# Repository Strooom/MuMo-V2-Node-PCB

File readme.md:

# Lora-based environmental monitor
* intended for monitoring collection items in musea. Other applications are possible but the unit is currently designed for indoor use only
* monitors temperature, relative humidity, VOC gasses, barometric pressure, light intensity and others
	- BME680 and TSL25911 sensors are built in, other can be added through I2C or UART
* runs on a single cell LiFePO4 battery. Battery-charger from USB-C port included
* Wio-E5 LoRa module from www.seeedstudio.com. This contains an STM32WLE processor combined with Semtech SX126X radio. The firmware runs directly on the STM32. More info on this Wio-E5 :  https://www.seeedstudio.com/LoRa-E5-Wireless-Module-p-4745.html
* 128 KByte of onboard EEPROM allows to buffer sensor-readings when network is unavailable.
* ePaper display allows to identify the device, and read status from the display, while still being ultra low power.

The related firmware for this device can be found in https://github.com/Strooom/MuMo-v2-Node-SW

More info can be found in the Wiki : 
https://github.com/Strooom/MuMo-V2-Node-PCB/wiki

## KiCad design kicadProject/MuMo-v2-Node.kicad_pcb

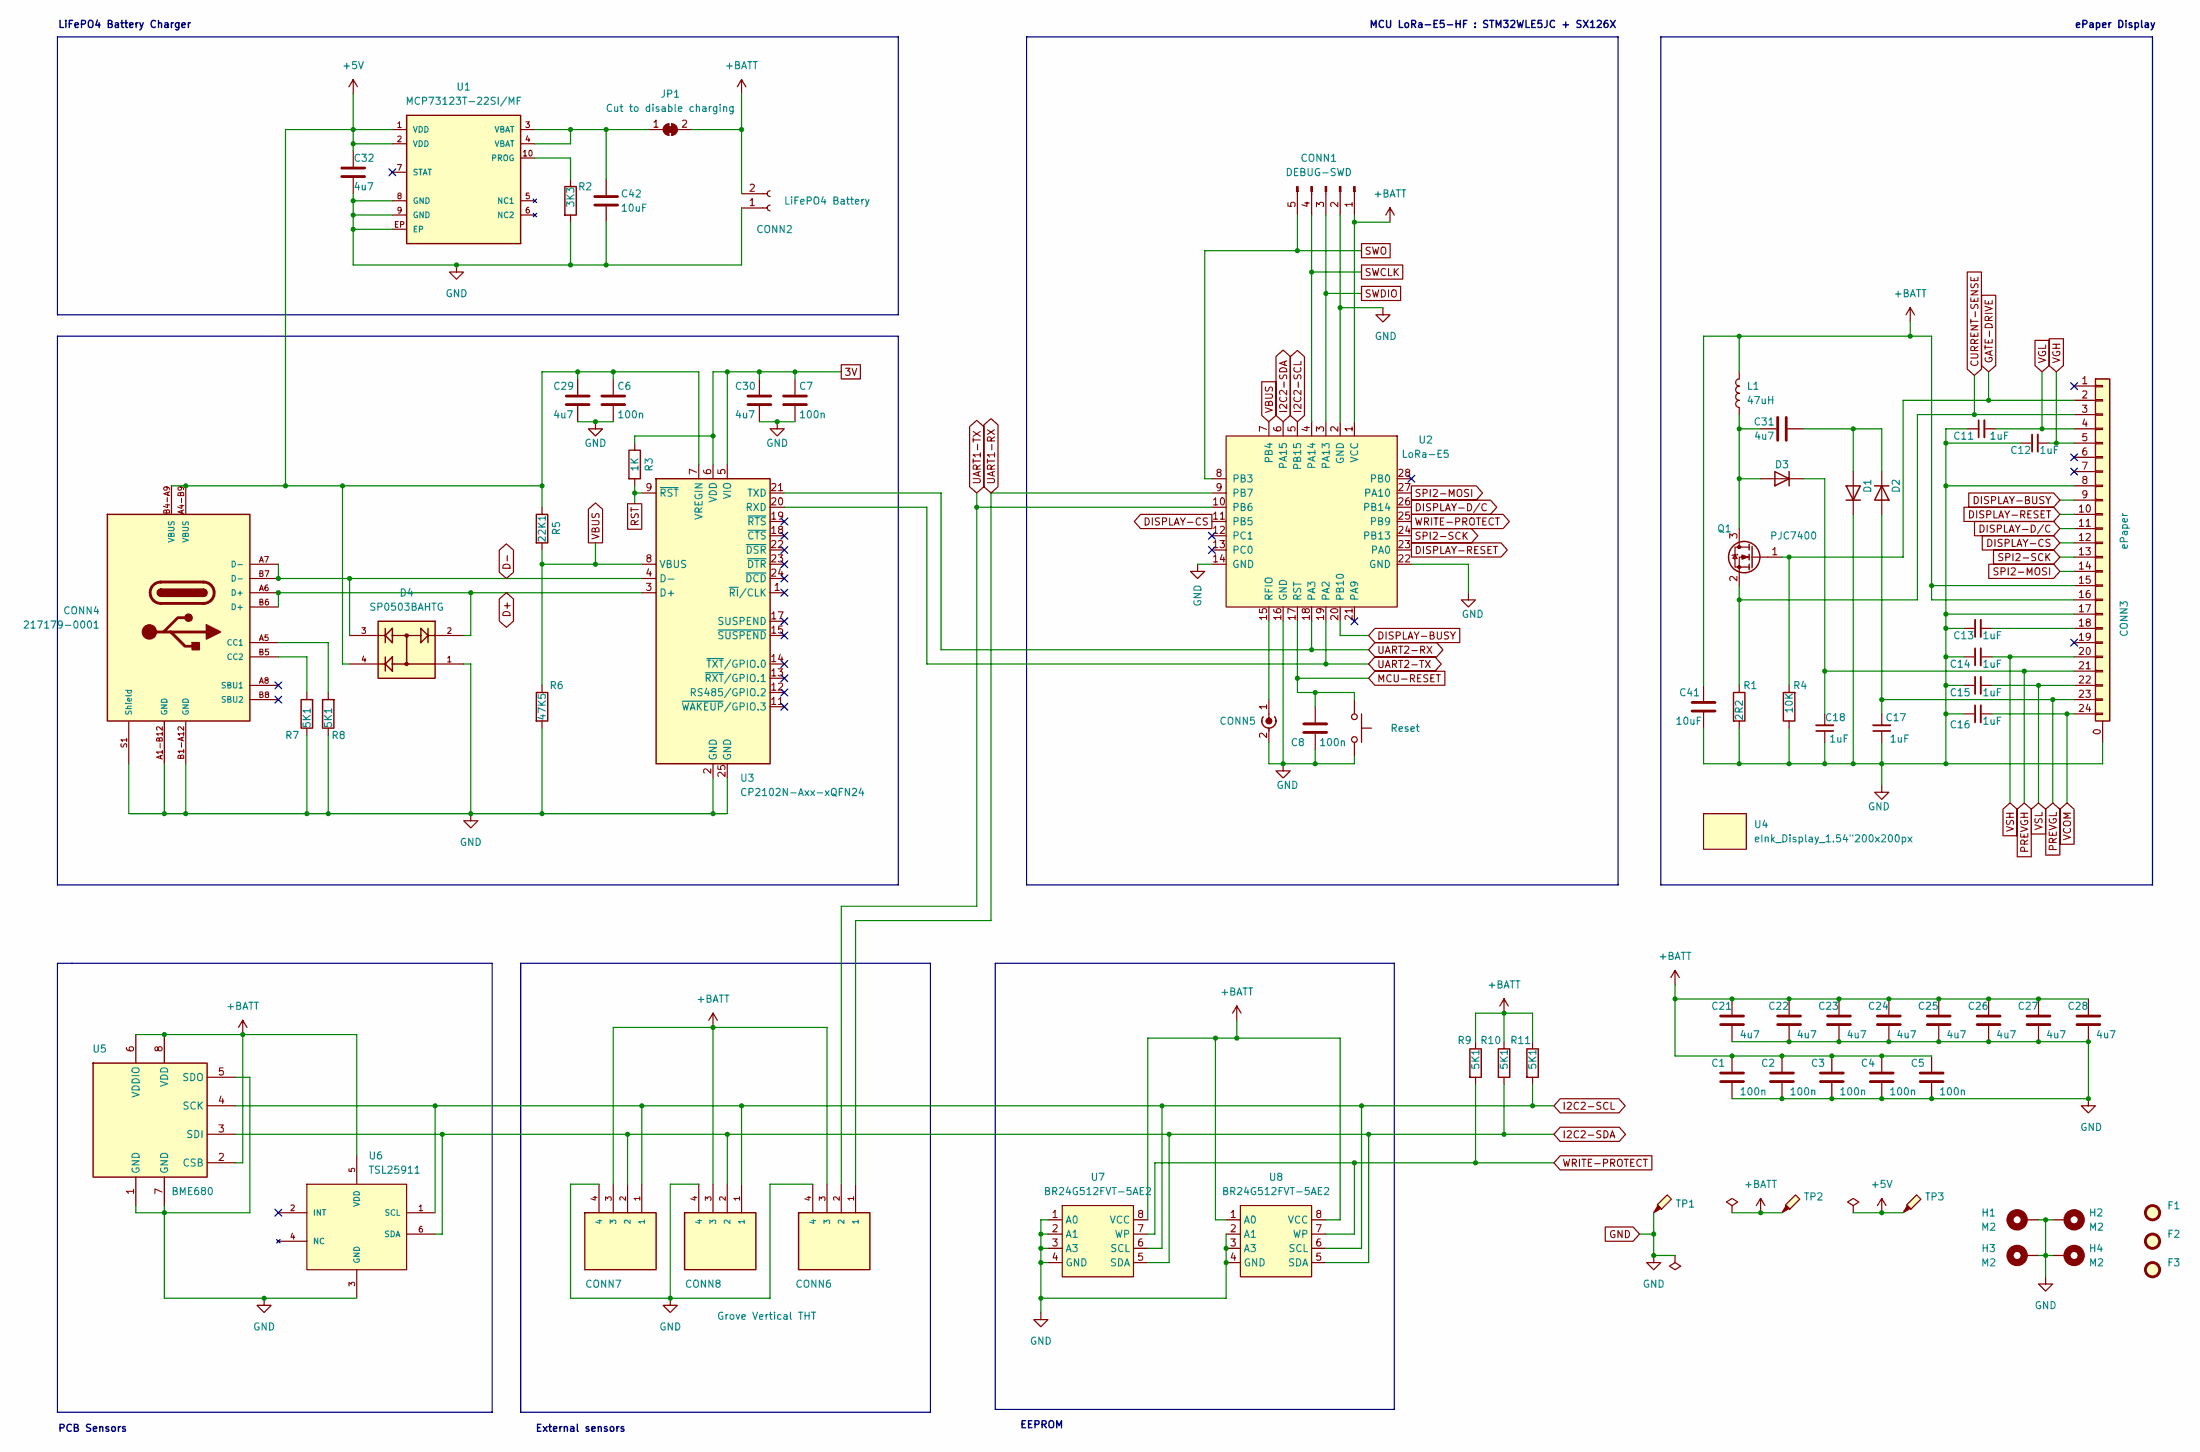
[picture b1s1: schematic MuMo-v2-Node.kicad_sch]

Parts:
C1, C2, C3, C4, C5, C6, C7, C8: 100n; 0603_1608Metric; MPN CGA3E2X7R1E104K080AA
C11, C12, C13, C14, C15, C16, C17, C18: 1uF; 0603_1608Metric; MPN CGA3E1X7R1E105K080AC
C21, C22, C23, C24, C25, C26, C27, C28, C29, C30, C31, C32: 4u7; 0603_1608Metric; MPN C1608X7S1A475K080AC
C41, C42: 10uF; 0603_1608Metric; MPN C1608X6S1A106M080AC
CONN1: DEBUG-SWD; PinHeader_1x05_P2.54mm_Vertical; MPN 10129378-905002BLF
CONN2: B2B-XH-A (LF)(SN); JST_XH_B2B-XH-A_1x02_P2.50mm_Vertical; MPN B2B-XH-A (LF)(SN)
CONN3: ePaper; TE_2-1734839-4_1x24-1MP_P0.5mm_Horizontal; MPN 2-1734839-4
CONN4: 217179-0001; Molex-2171790001; PARTREV A3
CONN5: Conn_Coaxial_Power; LINX_CONSMA020.062-G; MPN CONSMA020.062-G
CONN6, CONN7, CONN8: Grove Vertical THT; SEEED_110990030; MPN 110990030
D1, D2, D3: SS1FL3HM3/H; D_SMF; MPN SL03-GS08
D4: SP0503BAHTG; SP0503BAHTG-SOT143; PARTREV N/A
F1, F2, F3: Fiducial; Fiducial_0.75mm_Mask1.5mm; MPN notApplicable
H1, H2, H3, H4: M2; MountingHole_2.2mm_M2_Pad; MPN notApplicable
JP1: Cut to disable charging; SolderJumper-2_P1.3mm_Bridged2Bar_Pad1.0x1.5mm; MPN notApplicable
L1: 47uH; L_TDK_VLS6045EX; MPN VLS6045EX-470M
Q1: PJC7400; SOT-323_SC-70; MPN PJC7400_R1_00001
R1: 2R2; 0603_1608Metric; MPN ERJ-3RQJ2R2V
R2: 3K3; 0603_1608Metric; MPN CR0603-JW-332ELF
R3: 1K; 0603_1608Metric; MPN CR0603-JW-102ELF
R4: 10K; 0603_1608Metric; MPN CR0603-JW-103ELF
R5: 22K1; 0603_1608Metric; MPN CR0603-FX-2212ELF
R6: 47K5; 0603_1608Metric; MPN CR0603-FX-4752ELF
R7, R8, R9, R10, R11: 5K1; 0603_1608Metric; MPN CR0603-FX-5101ELF
SW1: Reset; SW_SPST_PTS815; MPN PTS815 SJM 250 SMTR LFS
TP1, TP2, TP3: testPad; TestPoint_THTPad_1.5x1.5mm_Drill0.7mm; MPN notApplicable
U1: MCP73123T-22SI/MF; DFN10 - MCP73123; MPN MCP73123T-22SI/MF
U2: LoRa-E5; MPN 317990687
U3: CP2102N-Axx-xQFN24; QFN24 - CP2102N; MPN CP2102N-A02-GQFN24R
U4: eInk_Display_1.54"200x200px; OSHW-Symbol_6.7x6mm_SilkScreen; MPN GDEH0154D67
U5: BME680; Bosch_BME680; MPN BME680
U6: TSL25911; TSL2591-SON; MPN TSL25911FN
U7, U8: BR24G512FVT-5AE2; TSSOP-B8; MPN BR24G512FVT-5AE2

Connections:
3V: C7.1, C30.1, R3.1, U3.5 (VIO), U3.6 (VDD)
+5V: C6.1, C29.1, C32.1, CONN4.A4-B9 (VBUS), CONN4.B4-A9 (VBUS), D4.4, R5.1, TP3.1, U1.1 (VDD), U1.2 (VDD), U3.7 (VREGIN)
+BATT: C1.1, C2.1, C3.1, C4.1, C5.1, C21.1, C22.1, C23.1, C24.1, C25.1, C26.1, C27.1, C28.1, C41.1, CONN1.1, CONN2.2 (+), CONN3.15, CONN3.16, CONN6.3, CONN7.3, CONN8.3, JP1.2 (B), L1.2, R9.1, R10.1, R11.1, TP2.1, U2.1 (VCC), U5.2 (CSB), U5.6 (VDDIO), U5.8 (VDD), U6.5 (VDD), U7.8 (VCC), U8.1 (A0), U8.8 (VCC)
CURRENT-SENSE: CONN3.3, Q1.2 (S), R1.1
D+: CONN4.A6 (D+), CONN4.B6 (D+), D4.2, U3.3 (D+)
D-: CONN4.A7 (D-), CONN4.B7 (D-), D4.3, U3.4 (D-)
DISPLAY-BUSY: CONN3.9, U2.20 (PB10)
DISPLAY-CS: CONN3.12, U2.11 (PB5)
DISPLAY-D/C: CONN3.11, U2.26 (PB14)
DISPLAY-RESET: CONN3.10, U2.23 (PA0)
GATE-DRIVE: CONN3.2, Q1.1 (G), R4.2
GND: C1.2, C2.2, C3.2, C4.2, C5.2, C6.2, C7.2, C8.2, C11.1, C12.1, C13.1, C14.1, C15.1, C16.1, C17.1, C18.1, C21.2, C22.2, C23.2, C24.2, C25.2, C26.2, C27.2, C28.2, C29.2, C30.2, C32.2, C41.2, C42.2, CONN1.2, CONN2.1 (-), CONN3.0 (GND), CONN3.8, CONN3.17, CONN4.A1-B12 (GND), CONN4.B1-A12 (GND), CONN4.S1 (Shield), CONN5.2 (Ext), CONN6.4, CONN7.4, CONN8.4, D1.1 (K), D4.1, H1.1, H2.1, H3.1, H4.1, R1.2, R2.2, R4.1, R6.2, R7.1, R8.1, SW1.1, TP1.1, U1.8 (GND), U1.9 (GND), U1.EP, U2.2 (GND), U2.14 (GND), U2.16 (GND), U2.22 (GND), U3.2 (GND), U3.25 (GND), U5.1 (GND), U5.5 (SDO), U5.7 (GND), U6.3 (GND), U7.1 (A0), U7.2 (A1), U7.3 (A3), U7.4 (GND), U8.2 (A1), U8.3 (A3), U8.4 (GND)
I2C2-SCL: CONN7.1, CONN8.1, R11.2, U2.5 (PB15), U5.4 (SCK), U6.1 (SCL), U7.6 (SCL), U8.6 (SCL)
I2C2-SDA: CONN7.2, CONN8.2, R10.2, U2.6 (PA15), U5.3 (SDI), U6.6 (SDA), U7.5 (SDA), U8.5 (SDA)
MCU-RESET: C8.1, SW1.2, U2.17 (RST)
unnamed: C13.2, CONN3.18
unnamed: CONN4.A5 (CC1), R8.2
unnamed: CONN4.B5 (CC2), R7.2
unnamed: CONN5.1 (In), U2.15 (RFIO)
unnamed: C31.1, D1.2 (A), D2.1 (K)
unnamed: C31.2, D3.2 (A), L1.1, Q1.3 (D)
unnamed: C42.1, JP1.1 (A), U1.3 (VBAT), U1.4 (VBAT)
unnamed: R2.1, U1.10 (PROG)
PREVGH: C18.2, CONN3.21, D3.1 (K)
PREVGL: C17.2, CONN3.23, D2.2 (A)
RST: R3.2, U3.9 (~RST)
SPI2-MOSI: CONN3.14, U2.27 (PA10)
SPI2-SCK: CONN3.13, U2.24 (PB13~)
SWCLK: CONN1.4, U2.4 (PA14)
SWDIO: CONN1.3, U2.3 (PA13)
SWO: CONN1.5, U2.8 (PB3)
UART1-RX: CONN6.1, U2.9 (PB7)
UART1-TX: CONN6.2, U2.10 (PB6)
UART2-RX: U2.18 (PA3), U3.21 (TXD)
UART2-TX: U2.19 (PA2), U3.20 (RXD)
VBUS: R5.2, R6.1, U2.7 (PB4), U3.8 (VBUS)
VCOM: C16.2, CONN3.24
VGH: C12.2, CONN3.5
VGL: C11.2, CONN3.4
VSH: C14.2, CONN3.20
VSL: C15.2, CONN3.22
WRITE-PROTECT: R9.2, U2.25 (PB9), U7.7 (WP), U8.7 (WP)

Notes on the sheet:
ePaper Display
LiFePO4 Battery Charger
EEPROM
External sensors
PCB Sensors
MCU LoRa-E5-HF : STM32WLE5JC + SX126X

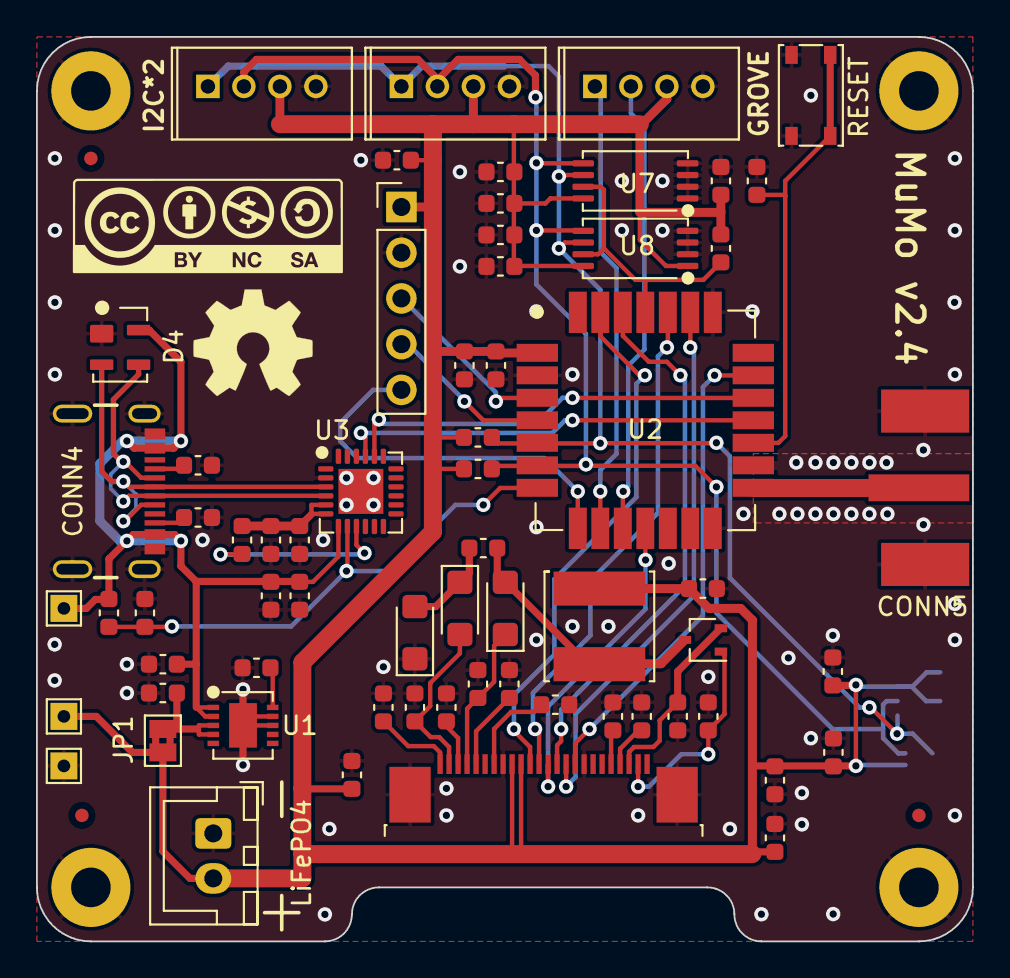
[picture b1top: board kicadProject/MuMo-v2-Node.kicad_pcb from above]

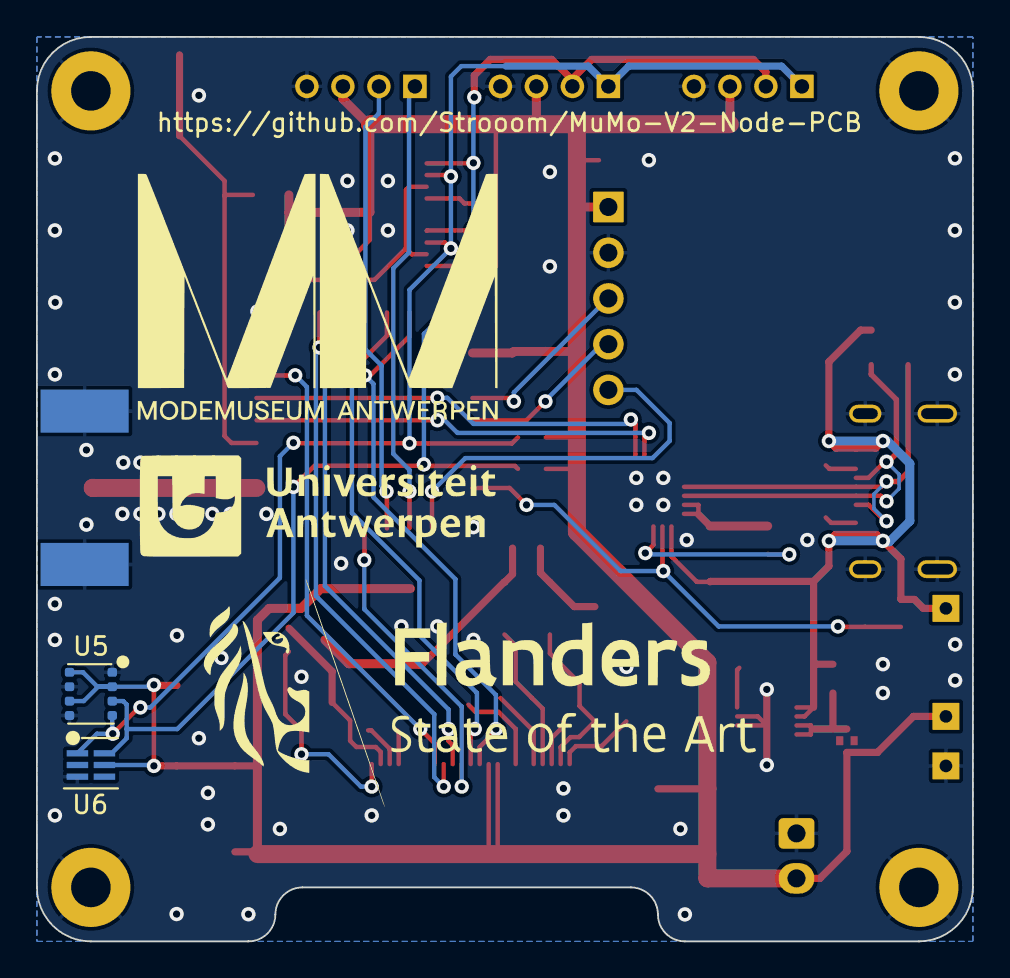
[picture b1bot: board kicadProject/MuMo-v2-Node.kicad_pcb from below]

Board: 2 copper layers, 52.0 x 50.3 mm, 75 parts (2 on the bottom side), 42 nets.

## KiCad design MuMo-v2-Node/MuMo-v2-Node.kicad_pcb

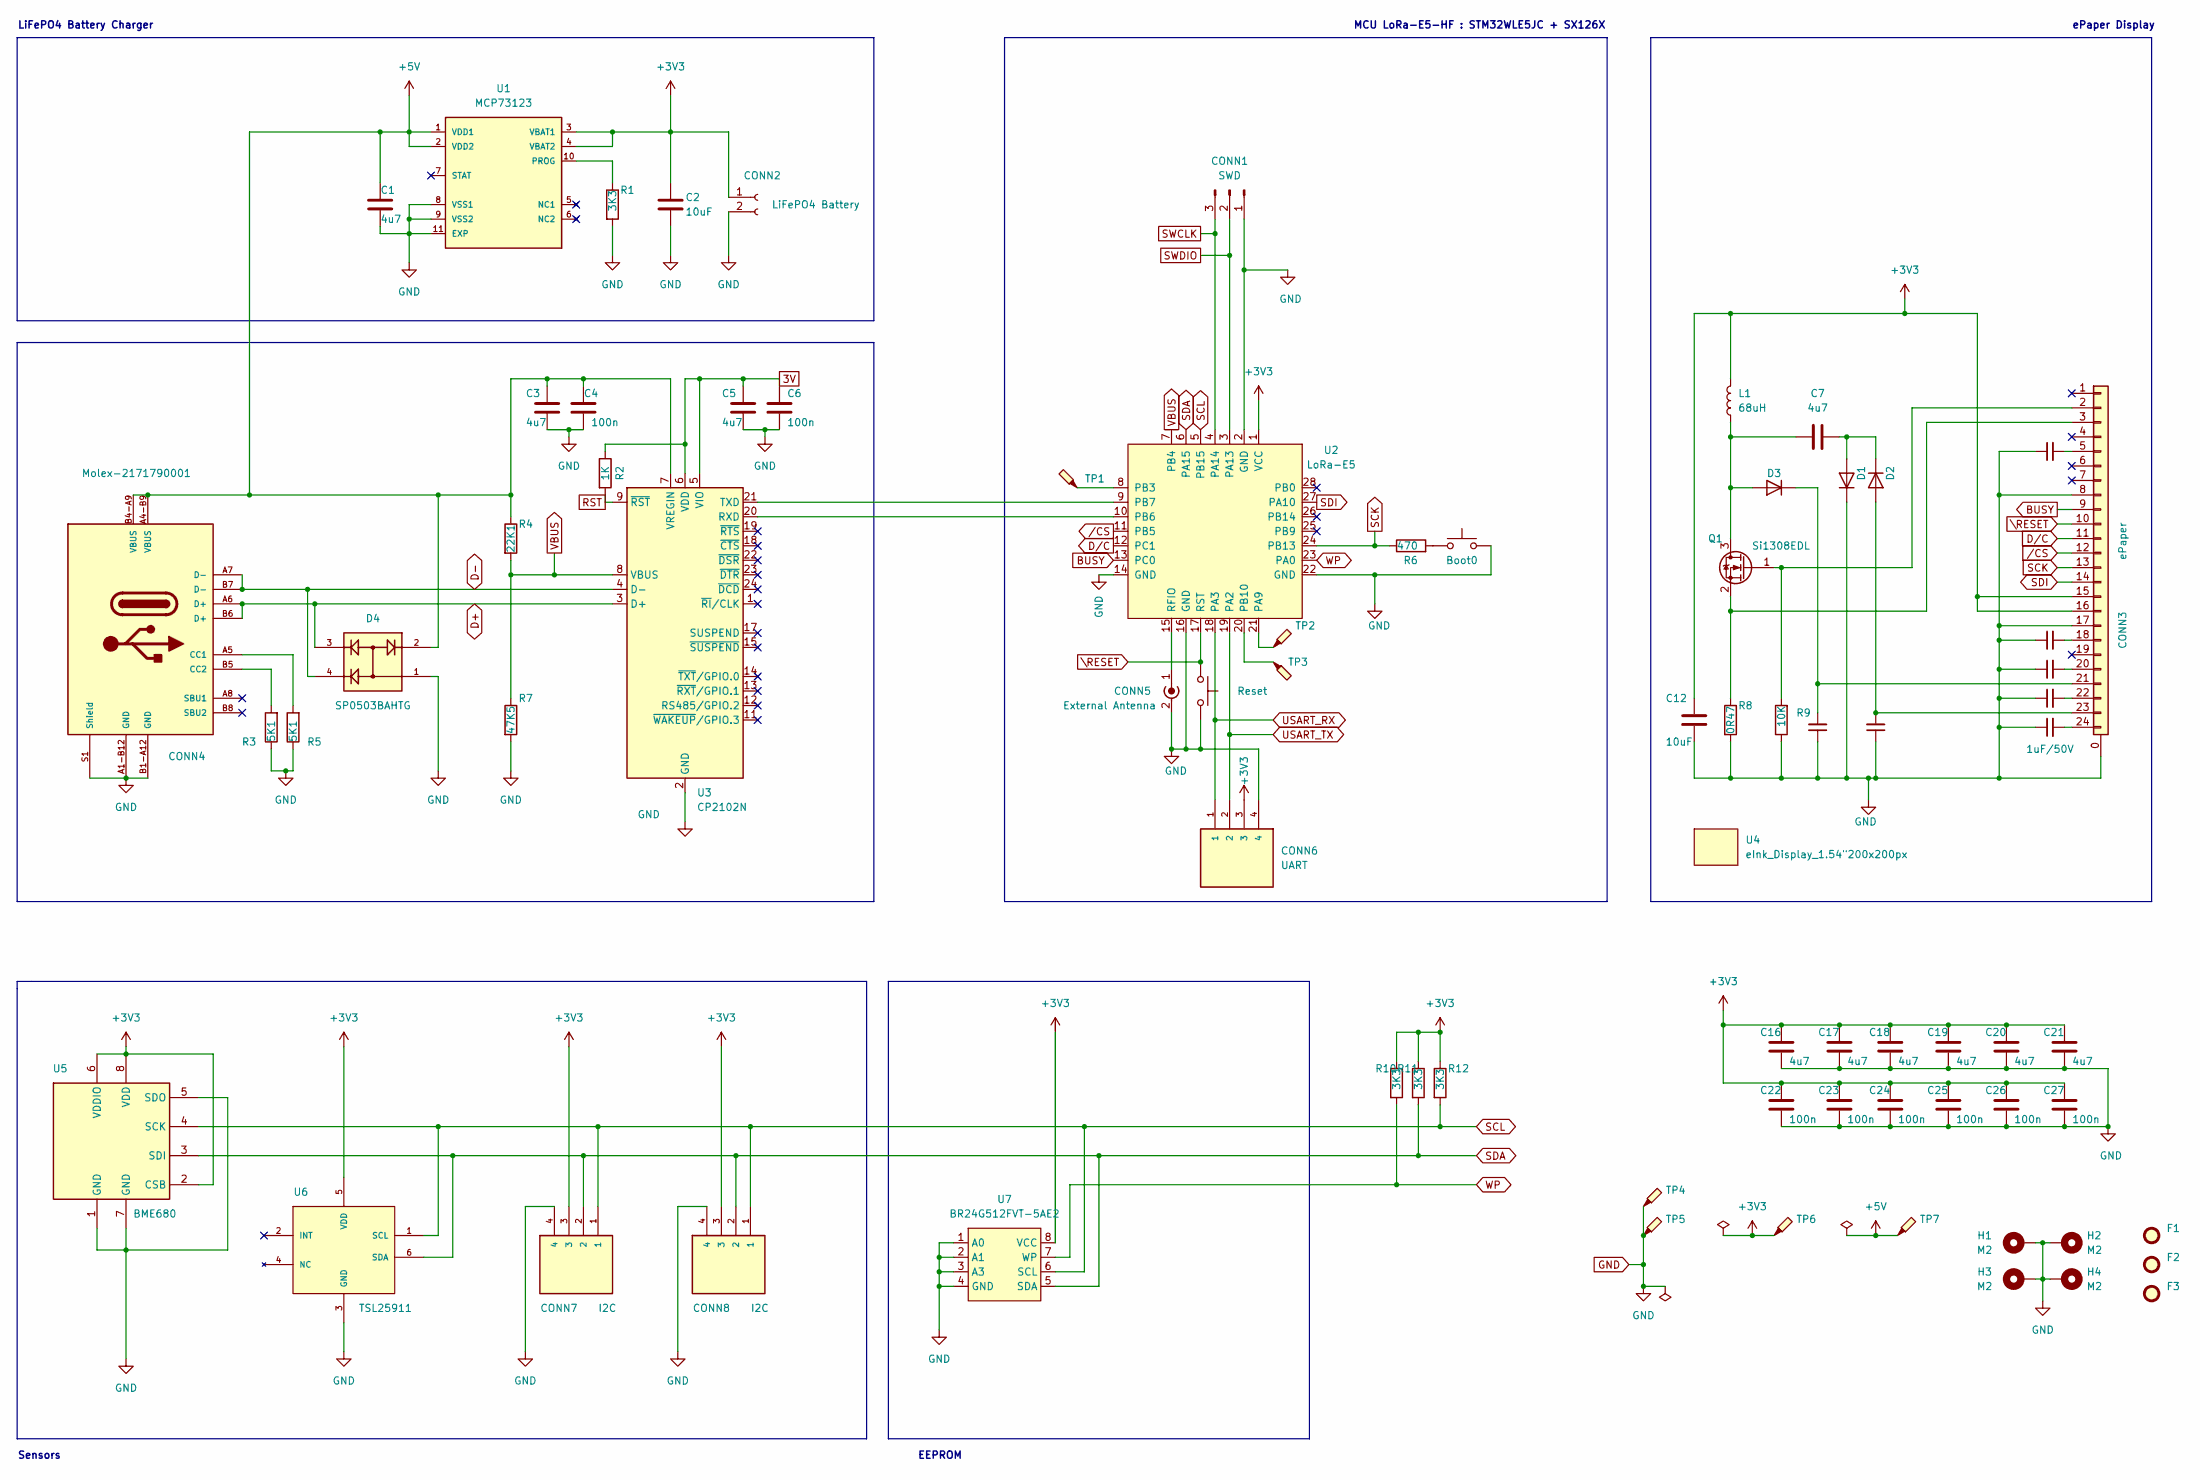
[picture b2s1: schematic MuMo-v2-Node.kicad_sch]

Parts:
C1, C3, C5, C7, C16, C17, C18, C19, C20, C21: 4u7; 0603_1608Metric; mpn C1608X7S1A475K080AC
C2, C12: 10uF; 0603_1608Metric; mpn C1608X6S1A106M080AC
C4, C6, C22, C23, C24, C25, C26, C27: 100n; 0603_1608Metric; mpn CGA3E2X7R1E104K080AA
C8, C9, C10, C11, C13, C14, C15: 1uF/50V; 0603_1608Metric; mpn C1608X5R1H105K080AB
CONN1: SWD; PinHeader_1x03_P2.54mm_Vertical; mpn 10129378-903001BLF
CONN2: B2B-XH-A (LF)(SN); JST_XH_B2B-XH-A_1x02_P2.50mm_Vertical; mpn B2B-XH-A (LF)(SN)
CONN3: ePaper; TE_2-1734839-4_1x24-1MP_P0.5mm_Horizontal; mpn 2-1734839-4
CONN4: Molex-2171790001; PARTREV A3
CONN5: External Antenna; LINX_CONSMA020.062-G; mpn CONSMA020.062-G
CONN6: UART; Grove_Vertical; PARTREV A
CONN7, CONN8: I2C; Grove_Vertical; PARTREV A
D1, D2, D3: SL03-GS08; D_SMF; mpn SL03-GS08
D4: SP0503BAHTG; SP0503BAHTG-SOT143; PARTREV N/A
F1, F2, F3: Fiducial; Fiducial_0.75mm_Mask1.5mm; mpn notApplicable
H1, H2, H3, H4: M2; MountingHole_2.2mm_M2_Pad; mpn notApplicable
L1: 68uH; L_TDK_VLS6045EX; mpn VLS6045EX-680M
Q1: Si1308EDL; SOT-323_SC-70; mpn SI1308EDL-T1-GE3
R1, R10, R11, R12: 3K3; 0603_1608Metric; mpn CR0603-JW-332ELF
R2: 1K; 0603_1608Metric; mpn CR0603-JW-102ELF
R3, R5: 5K1; 0603_1608Metric; mpn CR0603-FX-5101ELF
R4: 22K1; 0603_1608Metric; mpn CR0603-FX-2212ELF
R6: 470; 0603_1608Metric; mpn CR0603-FX-4700ELF
R7: 47K5; 0603_1608Metric; mpn CR0603-FX-4752ELF
R8: 0R47; 0603_1608Metric; mpn ERJ-3RQFR47V
R9: 10K; 0603_1608Metric; mpn CR0603-JW-103ELF
SW1: Boot0; SW_SPST_PTS815; mpn PTS815 SJM 250 SMTR LFS
SW2: Reset; SW_SPST_PTS815; mpn PTS815 SJM 250 SMTR LFS
TP1, TP2, TP3: GND; TestPoint_THTPad_1.5x1.5mm_Drill0.7mm; mpn notApplicable
TP4, TP5: GND; TestPoint_THTPad_2.5x2.5mm_Drill1.2mm; mpn notApplicable
TP6: 3V3; TestPoint_THTPad_2.5x2.5mm_Drill1.2mm; mpn notApplicable
TP7: TestPoint_Probe; TestPoint_THTPad_2.5x2.5mm_Drill1.2mm; mpn notApplicable
U1: MCP73123; DFN10; mpn MCP73123-22SI/MF
U2: LoRa-E5; mpn 317990687
U3: CP2102N; QFN24 - CP2102N; mpn CP2102N-A02-GQFN24
U4: eInk_Display_1.54"200x200px; OSHW-Symbol_6.7x6mm_SilkScreen; mpn GDEH0154D67
U5: BME680; Bosch_BME680; mpn BME680
U6: TSL25911; TSL2591-SON; PARTREV v1-01
U7: BR24G512FVT-5AE2; TSSOP-B8; mpn BR24G512FVT-5AE2

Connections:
3V: C5.1, C6.1, R2.1, U3.5 (VIO), U3.6 (VDD)
+3V3: C2.1, C12.1, C16.1, C17.1, C18.1, C19.1, C20.1, C21.1, C22.1, C23.1, C24.1, C25.1, C26.1, C27.1, CONN2.1 (BAT+), CONN3.15, CONN3.16, CONN6.3, CONN7.3, CONN8.3, L1.2, R10.1, R11.1, R12.1, TP6.1, U1.3 (VBAT1), U1.4 (VBAT2), U2.1 (VCC), U5.2 (CSB), U5.6 (VDDIO), U5.8 (VDD), U6.5 (VDD), U7.8 (VCC)
+5V: C1.1, C3.1, C4.1, CONN4.A4-B9 (VBUS), CONN4.B4-A9 (VBUS), D4.2, R4.1, TP7.1, U1.1 (VDD1), U1.2 (VDD2), U3.7 (VREGIN)
BUSY: CONN3.9, U2.13 (PC0)
D+: CONN4.A6 (D+), CONN4.B6 (D+), D4.3, U3.3 (D+)
D-: CONN4.A7 (D-), CONN4.B7 (D-), D4.4, U3.4 (D-)
D/C: CONN3.11, U2.12 (PC1)
GND: C1.2, C2.2, C3.2, C4.2, C5.2, C6.2, C8.1, C9.1, C10.1, C11.1, C12.2, C13.1, C14.1, C15.1, C16.2, C17.2, C18.2, C19.2, C20.2, C21.2, C22.2, C23.2, C24.2, C25.2, C26.2, C27.2, CONN1.1, CONN2.2 (BAT-), CONN3.0 (GND), CONN3.8, CONN3.17, CONN4.A1-B12 (GND), CONN4.B1-A12 (GND), CONN4.S1 (Shield), CONN5.2 (Ext), CONN6.4, CONN7.4, CONN8.4, D1.1 (K), D4.1, H1.1, H2.1, H3.1, H4.1, R1.2, R3.1, R5.1, R7.2, R8.2, R9.1, SW1.2, SW2.1, TP4.1, TP5.1, U1.8 (VSS1), U1.9 (VSS2), U1.11 (EXP), U2.2 (GND), U2.14 (GND), U2.16 (GND), U2.22 (GND), U3.2 (GND), U5.1 (GND), U5.5 (SDO), U5.7 (GND), U6.3 (GND), U7.1 (A0), U7.2 (A1), U7.3 (A3), U7.4 (GND)
unnamed: C7.1, D1.2 (A), D2.1 (K)
unnamed: C7.2, D3.2 (A), L1.1, Q1.3 (D)
unnamed: C8.2, CONN3.5
unnamed: C9.2, CONN3.18
unnamed: C10.2, CONN3.20
unnamed: C11.2, CONN3.22
unnamed: C13.2, CONN3.21, D3.1 (K)
unnamed: C14.2, CONN3.23, D2.2 (A)
unnamed: C15.2, CONN3.24
unnamed: CONN3.2, Q1.1 (G), R9.2
unnamed: CONN3.3, Q1.2 (S), R8.1
unnamed: CONN4.A5 (CC1), R5.2
unnamed: CONN4.B5 (CC2), R3.2
unnamed: CONN5.1 (In), U2.15 (RFIO)
unnamed: R1.1, U1.10 (PROG)
unnamed: R6.2, SW1.1
unnamed: TP1.1, U2.8 (PB3)
unnamed: TP2.1, U2.21 (PA9)
unnamed: TP3.1, U2.20 (PB10)
unnamed: U2.9 (PB7), U3.21 (TXD)
unnamed: U2.10 (PB6), U3.20 (RXD)
RST: R2.2, U3.9 (~RST)
SCK: CONN3.13, R6.1, U2.24 (PB13~)
SCL: CONN7.1, CONN8.1, R12.2, U2.5 (PB15), U5.4 (SCK), U6.1 (SCL), U7.6 (SCL)
SDA: CONN7.2, CONN8.2, R11.2, U2.6 (PA15), U5.3 (SDI), U6.6 (SDA), U7.5 (SDA)
SDI: CONN3.14, U2.27 (PA10)
SWCLK: CONN1.3, U2.4 (PA14)
SWDIO: CONN1.2, U2.3 (PA13)
USART_RX: CONN6.1, U2.18 (PA3)
USART_TX: CONN6.2, U2.19 (PA2)
VBUS: R4.2, R7.1, U2.7 (PB4), U3.8 (VBUS)
WP: R10.2, U2.23 (PA0), U7.7 (WP)
\RESET: CONN3.10, SW2.2, U2.17 (RST)
/CS: CONN3.12, U2.11 (PB5)

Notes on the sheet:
ePaper Display
LiFePO4 Battery Charger
EEPROM
Sensors
MCU LoRa-E5-HF : STM32WLE5JC + SX126X

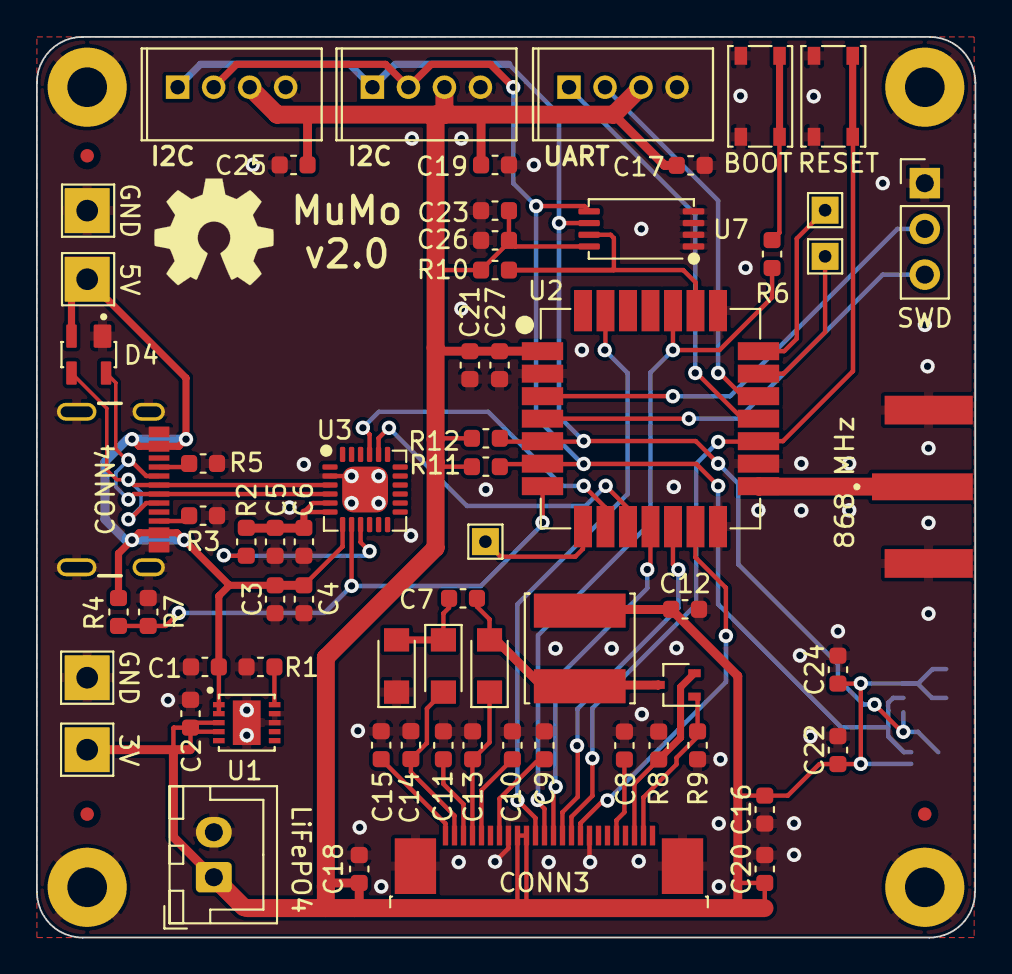
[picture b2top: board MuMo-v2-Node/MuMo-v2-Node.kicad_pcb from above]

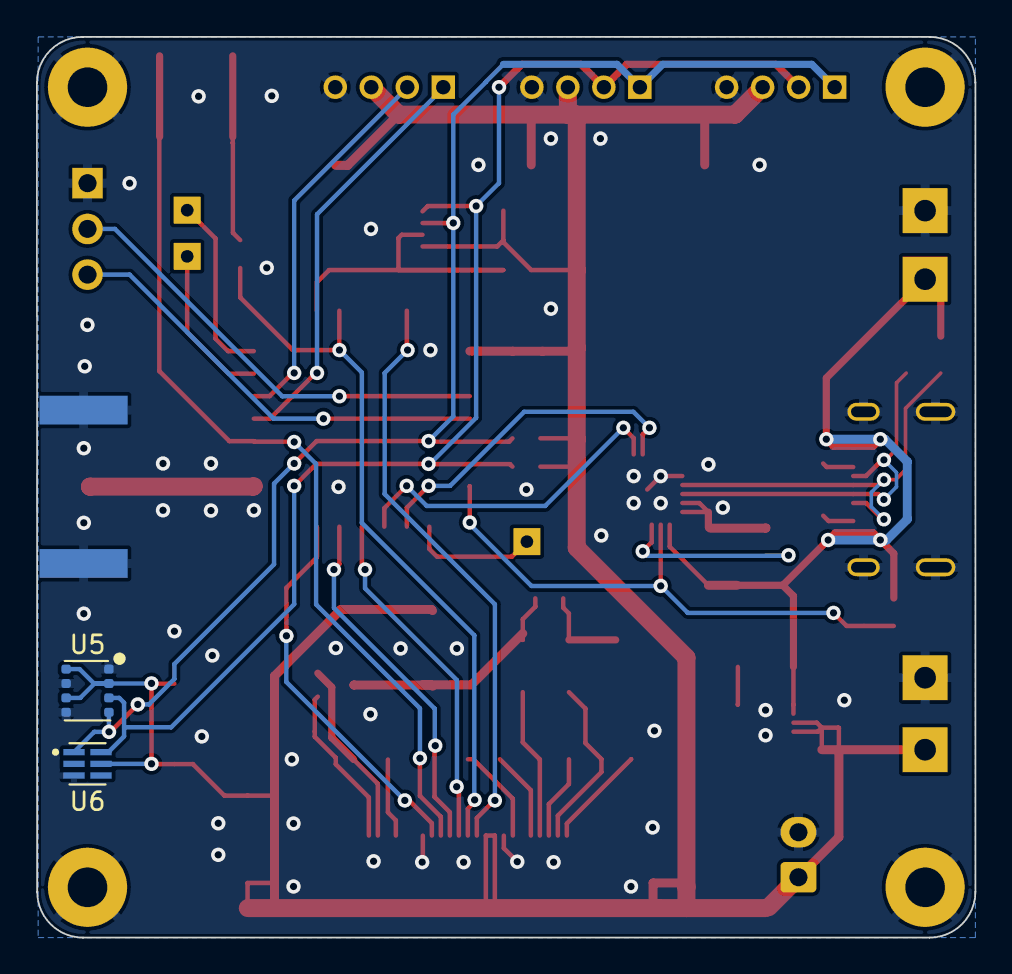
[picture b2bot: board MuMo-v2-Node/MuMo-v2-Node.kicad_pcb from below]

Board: 2 copper layers, 52.1 x 50.0 mm, 76 parts (2 on the bottom side), 42 nets.

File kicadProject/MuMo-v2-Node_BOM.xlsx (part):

Quantity | Designators | Description | Value | supplier1PartURL | Footprint | manufacturer | mpn | Datasheet | description | stock | supplier1Name | supplier1PartNumber | supplier2Name | supplier2PartNumber | supplier2PartURL
6 | C4 C6 C22 C24 C26 C27 | Multilayer Ceramic Capacitors MLCC - SMD/SMT CGA 0603 25V 0.1uF X7R 10% AEC-Q200 | 100n | https://www.mouser.be/ProductDetail/TDK/CGA3E2X7R1E104K080AA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 | 0603_1608Metric | TDK | CGA3E2X7R1E104K080AA | https://product.tdk.com/system/files/dam/doc/product/capacit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 | Multilayer Ceramic Capacitors MLCC - SMD/SMT CGA 0603 25V 0.1uF X7R 10% AEC-Q200 | 480000 | Mouser | 810-CGA3E2X7R1E104K | Digi-Key
12 | C1 C3 C5 C7 C16 C17 C18 C19 C20 C21 C23 C25 | Multilayer Ceramic Capacitors MLCC - SMD/SMT 0603 10V 4.7uF X7S 10% T: 0.8mm | 4u7 | https://www.mouser.be/ProductDetail/TDK/C1608X7S1A475K080AC?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 | 0603_1608Metric | TDK | C1608X7S1A475K080AC CGA3E2X7R1E104K080AA | https://product.tdk.com/system/files/dam/doc/product/capacit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 | Multilayer Ceramic Capacitors MLCC - SMD/SMT 0603 10V 4.7uF X7S 10% T: 0.8mm Mu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 | 660000 480000 | Mouser | 810-C1608X7S1A475KAC 810-CGA3E2X7R1E104K | Digi-Key
2 | C2 C12 | Multilayer Ceramic Capacitors MLCC - SMD/SMT 0603 10V 10uF X6S 10% T:0.8mm 20% | 10uF | https://www.mouser.be/ProductDetail/TDK/C1608X6S1A106M080AC?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 | 0603_1608Metric | TDK | C1608X6S1A106M080AC | https://product.tdk.com/system/files/dam/doc/product/capacit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 | Multilayer Ceramic Capacitors MLCC - SMD/SMT 0603 10V 10uF X6S 10% T:0.8mm 20% | 180000 | Mouser | 810-C1608X6S1A106M | Digi-Key
7 | C8 C9 C10 C11 C13 C14 C15 | Multilayer Ceramic Capacitors MLCC - SMD/SMT 0603 50VDC 1uF 10% X5R 0.8mm | 1uF/50V | https://www.mouser.be/ProductDetail/TDK/C1608X5R1H105K080AB?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 | 0603_1608Metric | TDK | C1608X5R1H105K080AB | https://product.tdk.com/system/files/dam/doc/product/capacit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 | Multilayer Ceramic Capacitors MLCC - SMD/SMT 0603 50VDC 1uF 10% X5R 0.8mm | 600000 | Mouser | 810-C1608X5R1H105K | Digi-Key
1 | CONN2 | JST XH 2pin THT Vertical | B2B-XH-A (LF)(SN) | https://be.farnell.com/jst-japan-solderless-terminals/b2b-xh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 | JST_XH_B2B-XH-A_1x02_P2.50mm_Vertical | JST | B2B-XH-A (LF)(SN) | https://www.farnell.com/datasheets/2057209.pdf | JST XH 2pin THT Vertical | 1500000 | Farnell | 1516276 | Digi-Key | 455-2247-ND | https://www.digikey.be/nl/products/detail/jst-sales-america-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
1 | CONN5 | RF-stekkers/Coaxiale stekkers SMA, Edge Mount, Female Receptacle, 0.062" PCB Mo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 | External Antenna | https://www.mouser.be/ProductDetail/Linx-Technologies/CONSMA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 | LINX_CONSMA020.062-G | Linx Technologies | CONSMA020.062-G | https://www.mouser.be/datasheet/2/238/LNNC_S_A0009753564_1-2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 | RF-stekkers/Coaxiale stekkers SMA, Edge Mount, Female Receptacle, 0.062" PCB Mo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 | 6400 | Mouser | 712-CONSMA020.062-G | Digi-Key | 343-CONSMA020.062-G-ND | https://www.digikey.be/nl/products/detail/linx-technologies-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
1 | CONN7 | Grove THT Vertical PCB Male connector | I2C | https://www.mouser.be/ProductDetail/Seeed-Studio/110990030?q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 | Grove_Vertical | Seeed Technology | 110990030 | https://www.mouser.be/datasheet/2/744/3470130P1-2525642.pdf | Grove THT Vertical PCB Male connector | notApplicable | Mouser | 713-110990030 | Digi-Key | 1597-1082-ND | https://www.digikey.be/nl/products/detail/seeed-technology-c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
1 | CONN8 | Grove THT Vertical PCB Male connector | I2C | https://www.mouser.be/ProductDetail/Seeed-Studio/110990030?q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 | Grove_Vertical | Seeed Technology | 110990030 | https://www.mouser.be/datasheet/2/744/3470130P1-2525642.pdf | Grove THT Vertical PCB Male connector | notApplicable | Mouser | 713-110990030 | Digi-Key | 1597-1082-ND | https://www.digikey.be/nl/products/detail/seeed-technology-c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
1 | CONN4 | USB-C receptable | Molex-2171790001 | https://www.mouser.be/ProductDetail/Molex/217179-0001?qs=DRk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 | Molex-2171790001 | Molex | 2171790001 | https://www.mouser.be/datasheet/2/837/USB4105-2888174.pdf | USB-C receptable | 18000 | Mouser | 538-217179-0001 | Digi-Key | 900-2171790001CT-ND | https://www.digikey.be/nl/products/detail/molex/2171790001/1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
1 | CONN1 | 3-pin Header 2.54mm | SWD | https://www.mouser.be/ProductDetail/Amphenol-FCI/10129378-90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 | PinHeader_1x03_P2.54mm_Vertical | Amphenol FCI | 10129378-903001BLF | https://cdn.amphenol-cs.com/media/wysiwyg/files/documentatio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 | 3-pin Header 2.54mm | 16800 | Mouser | 649-1012937890301BLF | Digi-Key
1 | CONN6 | Grove THT Vertical PCB Male connector | UART | https://www.mouser.be/ProductDetail/Seeed-Studio/110990030?q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 | Grove_Vertical | Seeed Technology | 110990030 | https://www.mouser.be/datasheet/2/744/3470130P1-2525642.pdf | Grove THT Vertical PCB Male connector | notApplicable | Mouser | 713-110990030 | Digi-Key | 1597-1082-ND | https://www.digikey.be/nl/products/detail/seeed-technology-c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
1 | CONN3 | FFC & FPC connectoren FPC CONN 0.5MM PITCH T/C 24P | ePaper | https://www.mouser.be/ProductDetail/TE-Connectivity/2-173483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 | TE_2-1734839-4_1x24-1MP_P0.5mm_Horizontal | TE Connectivity | 2-1734839-4 | https://www.mouser.be/datasheet/2/418/7/ENG_CD_1734839_C_C_1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 | FFC & FPC connectoren FPC CONN 0.5MM PITCH T/C 24P | 9000 | Mouser | 571-2-1734839-4 | Digi-Key
2 | D1 D2 | Schottky-diodes & gelijkrichters 1.1A .395V | SL03-GS08 | https://www.mouser.be/ProductDetail/Vishay-Semiconductors/SL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 | D_SMF | Vishay Semiconductors | SL03-GS08 | https://www.mouser.be/datasheet/2/427/sl02-2898123.pdf | Schottky-diodes & gelijkrichters 1.1A .395V | 0 | Mouser | 625-SL03 | Digi-Key | SL03-GS08CT-ND | https://www.digikey.be/nl/products/detail/vishay-general-sem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
1 | D4 | TVS DIODE 5.5VWM 8.5VC SOT143 | SP0503BAHTG | https://www.mouser.be/ProductDetail/Littelfuse/SP0503BAHTG?q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 | SP0503BAHTG-SOT143 | Littelfuse | SP0503BAHTG | https://www.mouser.be/datasheet/2/240/Littelfuse_TVS_Diode_A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 | TVS DIODE 5.5VWM 8.5VC SOT143 | 200000 | Mouser | 576-SP0503BAHTG | Digi-Key | F2715CT-ND | https://www.digikey.be/nl/products/detail/littelfuse-inc/SP0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
1 | D3 | Schottky-diodes & gelijkrichters 1.1A .395V | SS1FL3HM3/H | https://www.mouser.be/ProductDetail/78-SS1FL3HM3-H | D_SMF | Vishay Semiconductors | SS1FL3HM3/H | https://www.mouser.be/datasheet/2/427/sl02-2898123.pdf | Schottky-diodes & gelijkrichters 1.1A .395V | 30000 | Mouser | 78-SS1FL3HM3/H
1 | L1 | Power Inductors - SMD 68uH | 68uH | https://www.mouser.be/ProductDetail/TDK/VLS6045EX-680M?qs=oF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 | L_TDK_VLS6045EX | TDK | VLS6045EX-680M | https://product.tdk.com/system/files/dam/doc/product/inducto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 | Power Inductors - SMD 68uH | 29000 | Mouser | 810-VLS6045EX-680M | Digi-Key
1 | Q1 | MOSFET 30V Vds 12V Vgs SC70-3 | PJC7400 | https://www.mouser.be/ProductDetail/241-PJC7400_R1_00001 | SOT-323_SC-70 | Panjit | PJC7400_R1_00001 | https://www.mouser.be/datasheet/2/427/si1308edl-1764588.pdf | MOSFET 30V Vds 12V Vgs SC70-3 | 26000 | Mouser | 241-PJC7400_R1_00001
1 | R8 | Current Sense Resistors - SMD 0603 0.47ohm 1% Curr Sense AEC-Q200 | 0R47 | https://www.mouser.be/ProductDetail/Panasonic/ERJ-3RQFR47V?q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 | 0603_1608Metric | Panasonic | ERJ-3RQFR47V | https://www.mouser.be/datasheet/2/315/AOA0000C313-1141758.pdf | Current Sense Resistors - SMD 0603 0.47ohm 1% Curr Sense AEC-Q200 | 160000 | Mouser | 667-ERJ-3RQFR47V | Digi-Key
1 | R6 | Thick Film Resistors - SMD 0603 470OHMS 5% 1/10WATT | 470 | https://www.mouser.be/ProductDetail/Bourns/CR0603-FX-4700ELF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 | 0603_1608Metric | Bourns | CR0603-FX-4700ELF | https://www.mouser.be/datasheet/2/54/cr-1858361.pdf | Thick Film Resistors - SMD 0603 470OHMS 5% 1/10WATT | notApplicable | Mouser | 652-CR0603FX-4700ELF | Digi-Key
1 | R2 | Thick Film Resistors - SMD 0603 1KOHMS 5% 1/10WATT | 1K | https://www.mouser.be/ProductDetail/Bourns/CR0603-JW-102ELF?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 | 0603_1608Metric | Bourns | CR0603-JW-102ELF | https://www.mouser.be/datasheet/2/54/cr-1858361.pdf | Thick Film Resistors - SMD 0603 1KOHMS 5% 1/10WATT | notApplicable | Mouser | 652-CR0603-JW-102ELF | Digi-Key
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
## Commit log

2022-12-29 V0,1
    added all datasheets
    schematic complete
    PCB layout complete
2022-12-29 cleaned datasheets
2022-12-29 added GND vias
2022-12-29 Add images & pdfs
2022-12-30 add gitignore
2022-12-30 update
    remove KiCAD backups from git repo
2022-12-30 add readme
2022-12-30 add license CC AT-NC-SA
2022-12-30 improve gitignore
2022-12-30 moved images to root
2022-12-30 add image
2022-12-30 add link to firmware
2022-12-30 update todo's
2022-12-31 fixed #1
    Replaced GCT4085 connector with Molex 2171790001
2023-01-03 Implemented improvements
    #5 stitching vias
    #4 USB differential pair
    #6 components / values for epaper driver circuit
2023-01-05 add link to Seeed Wio-E5
2023-01-05 update project structure
    move the project libraries to a folder inside the KiCAD project
2023-01-05 uodate BOM with alternatives for 2 components that were out of stock
2023-01-05 add link to wiki
2023-02-07 V2.1
    Minor update, fixing issues #2 #3 #6 #7 #8 #9 #10 #11 #12 #13 #14 #15 #16 #17 #18 and #19
2023-02-07 cleanup references
    sequential numbering for all identical parts
2023-02-08 cleanup old BOM files
2023-02-08 added logo
    Flanders
    State of the Art
2023-02-20 Improving the BOM
    Grouped designators,
    Added logo to silkscreen
2023-02-20 updated rendered image
2023-02-20 renamed whatsnew
2023-02-21 updated gerbers for Seeed Studio Manufacturing
2023-03-01 update 128Kbyte EEPROM io 64K
2023-03-17 corrected battery connector
    To align with most common premade cables, pin 1 = GND, pin 2 - VBAT
2023-03-27 added first version of testplan
2023-05-04 add more images to readme
2023-05-04 more images explaining fucntional blocks
2023-05-04 add source for block diagrams
2023-07-26 V2.4
    Updated to Kicad V7
    * small design improvements, resolving the DRC of V7
    * ready for production at Aisler
2023-07-26 added polarity to pins of battery connector
